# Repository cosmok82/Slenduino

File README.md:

Slenduino
=========
<div style="text-align: center;">

</div>
<br>
Author: Cosimo Orlando.<br>
Blog: http://creativityslashdesign.tk/
<br>
Development Board (based on PIC12F683).
<br>
<br>
All info on my blog.
<br>
<br>
<br>
GPL v3 License

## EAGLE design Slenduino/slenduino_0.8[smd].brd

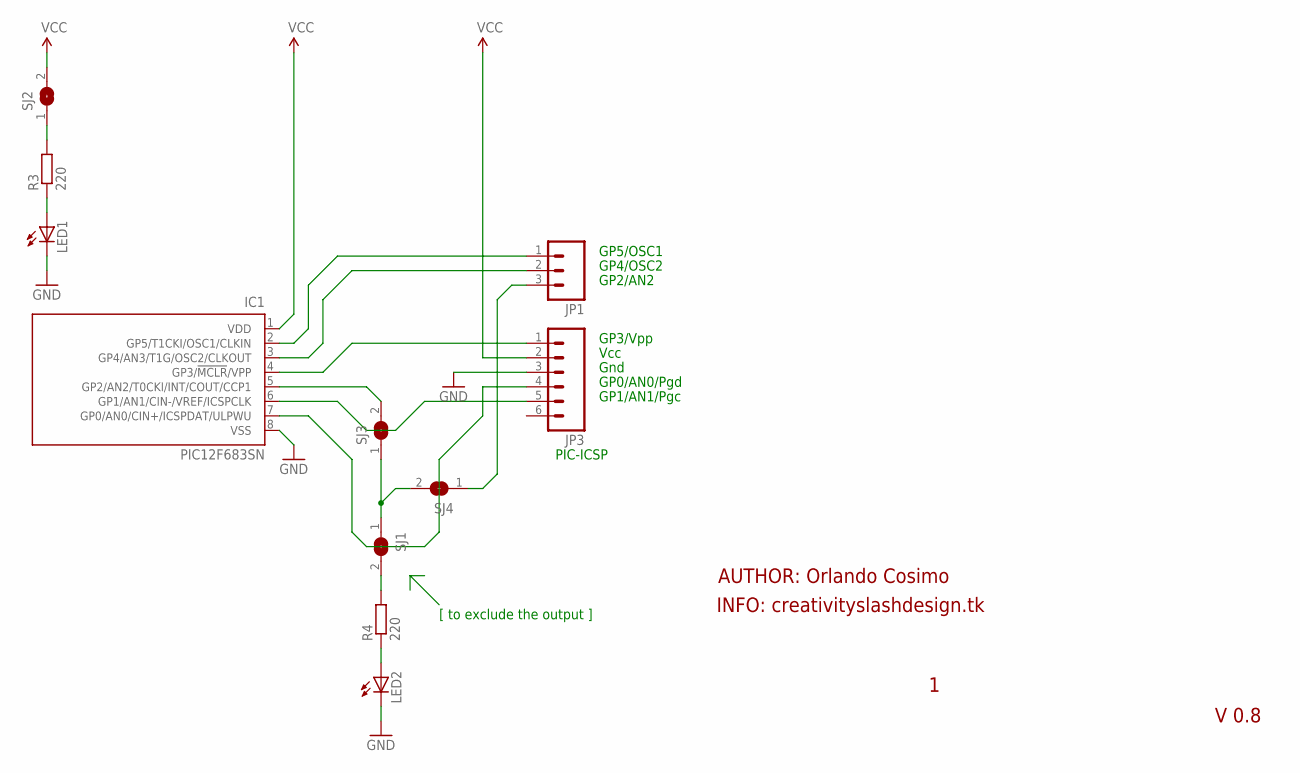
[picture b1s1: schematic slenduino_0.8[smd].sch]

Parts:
IC1: PIC12F683SN; SO-08
JP1: M03LOCK_LONGPADS; 1X03_LOCK_LONGPADS
JP3: M06LOCK_LONGPADS; 1X06_LOCK_LONGPADS
LED1, LED2: LEDCHIPLED_0805; CHIPLED_0805
R3, R4: 220; M1406
SJ1, SJ2, SJ3, SJ4: SJW

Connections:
GND: IC1.8 (VSS), JP3.3, LED1.C, LED2.C
unnamed: IC1.4 (GP3/!MCLR!/VPP), JP3.1
unnamed: IC1.6 (GP1/AN1/CIN-/VREF/ICSPCLK), JP3.5
unnamed: IC1.2 (GP5/T1CKI/OSC1/CLKIN), JP1.1
unnamed: IC1.5 (GP2/AN2/T0CKI/INT/COUT/CCP1), SJ3.2
unnamed: IC1.7 (GP0/AN0/CIN+/ICSPDAT/ULPWU), JP3.4
unnamed: R3.2, SJ2.1
unnamed: JP1.3, SJ4.1
unnamed: LED2.A, R4.1
unnamed: LED1.A, R3.1
unnamed: IC1.3 (GP4/AN3/T1G/OSC2/CLKOUT), JP1.2
unnamed: R4.2, SJ1.2
unnamed: SJ1.1, SJ3.1, SJ4.2
VCC: IC1.1 (VDD), JP3.2, SJ2.2

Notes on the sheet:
GP3/Vpp
Vcc
Gnd
GP0/AN0/Pgd
GP1/AN1/Pgc
PIC-ICSP
GP5/OSC1
GP4/OSC2
GP2/AN2
[ to exclude the output ]
V 0.8
INFO: creativityslashdesign.tk
AUTHOR: Orlando Cosimo

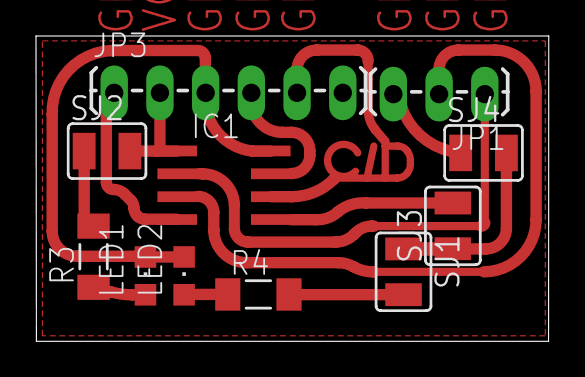
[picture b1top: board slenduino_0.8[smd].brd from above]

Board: 2 copper layers, 28.5 x 17.0 mm, 11 parts (0 on the bottom side), 14 nets.

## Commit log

2013-12-02 V 0.8
    First Version.
2013-12-02 Update README.md
    First edit.
2014-01-26 Tutorials [22-12-2013 / 22-01-2014]
    Tutorials:
    - The The Blinking LED
    - The Larson Scanner
